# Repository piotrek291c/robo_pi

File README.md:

# robo_pi

http://forbot.pl/blog/artykuly/teoria/jak-zaimplementowac-regulator-pid-dla-silnika-z-enkoderem-id6310
http://www.forbot.pl/forum/topics20/teoria-sterowanie-silnikiem-robotem-pid-vt2055.htm
http://forbot.pl/blog/artykuly/programowanie/sterowanie-robotem-mobilnym-klasy-20-id2708

http://www.forbot.pl/forum/topics43/pomoc-w-doborze-silnika-do-robota-vt6278.htm

https://oscarliang.com/raspberry-pi-color-tracking-opencv-pid/

https://oscarliang.com/raspberry-pi-color-tracking-opencv-pid/

http://robot-kingdom.com/pid-controller-tutorial-for-robots/

http://home.agh.edu.pl/~kwant/wordpress/wp-content/uploads/Praca-in%C5%BCynierska-Mateusz-Skalski.pdf

http://www.forbot.pl/forum/topics20/teoria-sterowanie-silnikiem-robotem-pid-vt2055.htm

http://forum.r-pi.pl/python/regulator-pid-t150544.html

https://github.com/DexterInd?tab=repositories

http://mikrokontrolery.blogspot.com/2011/03/Robotyka-Teoria-Predkosc-obrotowa-oraz-kierunek-obrotu-kol.html

http://www.jarzebski.pl/arduino/czujniki-i-sensory/3-osiowy-magnetometr-hmc5883l.html

https://projects.drogon.net/raspberry-pi/wiringpi/i2c-library/

https://github.com/sanzaru/hmc5883l

https://github.com/mwilliams03/BerryIMU

https://github.com/STMemsLinuxDrivers/lsm6ds3-input/blob/master/drivers/input/misc/lsm6ds3/lsm6ds3_i2c.c

https://github.com/sparkfun/SparkFun_LSM6DS3_Arduino_Library

http://raspberrypiprogramming.blogspot.com/2014/08/how-to-install-and-setup-qt-creator-on.html

http://raspberrypiprogramming.blogspot.com/2014/08/how-to-install-and-setup-qt-creator-on.html

https://blogs.ncl.ac.uk/francisfranklin/2014/04/16/using-i2c-with-the-raspberry-pi-step-2-sparkfun-9dof-sensor-stick/
https://github.com/jrowberg/i2cdevlib/tree/master/RaspberryPi_bcm2835
https://github.com/sparkfun/LSM6DS3_Breakout/blob/master/Libraries/Arduino/examples/MinimalistExample/MinimalistExample.ino

https://github.com/jrowberg/i2cdevlib
https://github.com/FJFranklin/i2cdevlib

https://github.com/mwbritton/Raspberry-Pi-4x4-in-Schools-Project/blob/master/LSM6DS3.py

https://github.com/sparkfun/SparkFun_LSM6DS3_Arduino_Library

https://github.com/me-no-dev/RasPiArduino

http://www.instructables.com/id/Building-a-segway-in-Raspberry-Pi/?ALLSTEPS

https://www.sunfounder.com/learn/sensor-kit-v2-0-for-raspberry-pi-b-plus/lesson-32-mpu6050-gyro-acceleration-sensor-sensor-kit-v2-0-for-b-plus.html

https://github.com/jrowberg/i2cdevlib/tree/master/RaspberryPi_bcm2835

https://github.com/jrowberg/i2cdevlib/tree/master/Arduino/MPU6050

https://github.com/mwilliams03/Raspberry-Gyro-Acc

http://www.jarzebski.pl/arduino/czujniki-i-sensory/czujnik-wilgotnosci-i-temperatury-dht11-dht22.html

http://www.raspberrypi-spy.co.uk/2013/10/analogue-sensors-on-the-raspberry-pi-using-an-mcp3008/

http://shaunsbennett.com/piblog/?p=266

https://github.com/halherta/RaspberryPi-mcp3008Spi

https://pimylifeup.com/raspberry-pi-webcam-server/

https://blog.miguelgrinberg.com/post/stream-video-from-the-raspberry-pi-camera-to-web-browsers-even-on-ios-and-android

https://blog.miguelgrinberg.com/post/how-to-build-and-run-mjpg-streamer-on-the-raspberry-pi

http://www.pyimagesearch.com/2015/03/30/accessing-the-raspberry-pi-camera-with-opencv-and-python/

https://github.com/ccrisan/motionpie/wiki/Fast-Network-Camera
https://blog.ligos.net/2016-04-17/RaspberryPi-As-A-Simple-MJPEG-Camera.html

http://www.howtoembed.com/projects/raspberry-pi/95-motioneye-with-raspberry-pi
https://github.com/ccrisan/motioneye/wiki/Install-On-Raspbian
https://programmaticponderings.com/2013/01/01/remote-motion-activated-web-based-video-surveillance-with-raspberry-pi/
http://pingbin.com/2012/12/raspberry-pi-web-cam-server-motion/

http://www.ostafichuk.com/raspberry-pi-projects/raspimower/fast-web-video-streaming-for-the-raspberry-pi/

https://github.com/dbblackdiamond/SparkFun-LSM6DS3-Photon

http://avrkwiat.nstrefa.pl/omnie/index.php?option=com_content&view=article&id=171&Itemid=195

https://github.com/sparkfun/SparkFun_LSM6DS3_Arduino_Library
http://robotics.stackexchange.com/questions/8680/calculating-position-based-on-accelerometer-data

http://www.starlino.com/imu_guide.html
http://perso-etis.ensea.fr/~pierandr/cours/M1_SIC/AN3397.pdf
http://aeroquad.com/showthread.php?7786-Simple-paper-about-an-algorithm-for-positioning-using-accelerometers

https://github.com/sparkfun/SparkFun_LSM6DS3_Arduino_Library/blob/master/src/SparkFunLSM6DS3.h

https://github.com/sparkfun/SparkFun_LSM6DS3_Arduino_Library/blob/master/src/SparkFunLSM6DS3.cpp

https://github.com/sparkfun/SparkFun_LSM6DS3_Arduino_Library/blob/master/examples/MinimalistExample/MinimalistExample.ino

https://github.com/dbblackdiamond/SparkFun-LSM6DS3-Photon/blob/master/firmware/SparkFun-LSM6DS3-Photon.h

http://pdf1.alldatasheet.net/datasheet-pdf/view/796179/STMICROELECTRONICS/LSM6DS3.html

http://avrkwiat.nstrefa.pl/omnie/index.php?option=com_content&view=article&id=245&Itemid=273

http://starter-kit.nettigo.pl/2013/03/robo-starter-kit-czyli-pierwsze-kroki-z-robotyka-line-follower/

http://akademia.nettigo.pl/playlist/robokit_od_nettigo.html

http://uczymy.edu.pl/wp/blog/2015/07/13/transoptor-szczelinowy/

https://botland.com.pl/transoptory-odbiciowe/52-czujnik-transoptor-odbiciowy-cny70.html

http://fritzing.org/media/fritzing-repo/projects/a/arduino-cny70-light-proximity-sensor/images/CNY70%20light%20proximity%20sensor_bb.png

https://github.com/cvra/odometry
https://github.com/srv/stereo_slam
http://automation.tkk.fi/attach/AS-0-2230/odometry.c.txt

http://rossum.sourceforge.net/papers/CalculationsForRobotics/CompendiumForKinematics.htm
https://github.com/eschulma/robot-libraries-arduino
https://arxiv.org/pdf/1509.02154.pdf
http://www.geology.smu.edu/dpa-www/robots/doc/odometry.txt
http://robotics.stackexchange.com/questions/1653/calculate-position-of-differential-drive-robot
http://robotics.stackexchange.com/questions/8693/how-to-perform-odometry-on-an-arduino-for-a-differential-wheeled-robot?rq=1
http://robotics.stackexchange.com/questions/8931/how-to-combine-odometry-information-with-time-shifted-information-from-imu?rq=1
https://firstinmaryland.org/images/stories/documents2013/2013_Educ_Day/Sensors_Presentation.pdf
http://kt.era.ee/supervision/Kallas2013.pdf
http://automation.tkk.fi/attach/AS-0-2230/odometry.c.txt
https://github.com/cvra/odometry

https://app.assembla.com/spaces/robot-autonomiczny/documents/b6JUyuJDir4ii4eJe5cbCb/download/b6JUyuJDir4ii4eJe5cbCb
http://lirec.iiar.pwr.edu.pl/~konarch/download/inne_roboty/zdarzenia_koncowe.pdf
https://app.assembla.com/spaces/robot-autonomiczny/documents/b6JUyuJDir4ii4eJe5cbCb/download/b6JUyuJDir4ii4eJe5cbCb

http://raspberrypi.stackexchange.com/questions/8851/setting-up-wifi-and-ethernet
https://sites.google.com/site/raspberryflightgear/4-qt-and-raspberry
https://www.raspberrypi.org/forums/viewtopic.php?t=33881
http://www.aoakley.com/articles/2013-07-31-raspberry-pi-networking.php

http://mdiy.pl/pcb-lutowanie-przelotek/
http://www.elektroda.pl/rtvforum/topic100099.html

http://rab.ict.pwr.wroc.pl/~arent/rr/mpr/czujniki0.html

http://howtomechatronics.com/projects/arduino-radar-project/

https://www.youtube.com/watch?v=I5nAynPdNJY

http://samselectronicsprojects.blogspot.com/2014/07/getting-roll-pitch-and-yaw-from-mpu-6050.html
http://www.jarzebski.pl/arduino/rozwiazania-i-algorytmy/odczyty-pitch-roll-oraz-filtr-kalmana.html
https://forum.arduino.cc/index.php?topic=407756.0
http://perso-etis.ensea.fr/%7Epierandr/cours/M1_SIC/AN3397.pdf

https://rasspberrypi.wordpress.com/2012/09/09/wifi-tools-for-raspberry-pi/

http://starter-kit.nettigo.pl/2012/02/akcelerometry-zyroskopy-i-kompasy-czyli-badanie-polozenia-z-arduino-cz-1/

https://pimylifeup.com/raspberry-pi-webcam-server/

https://www.element14.com/community/community/raspberry-pi/raspberrypi_projects/blog/2016/04/25/noir-v2-video-streaming-baby-monitor

https://blog.miguelgrinberg.com/post/stream-video-from-the-raspberry-pi-camera-to-web-browsers-even-on-ios-and-android

https://programmaticponderings.com/2013/01/01/remote-motion-activated-web-based-video-surveillance-with-raspberry-pi/

https://pimylifeup.com/raspberry-pi-security-camera/

https://www.element14.com/community/community/raspberry-pi/raspberrypi_projects/blog/2016/04/25/noir-v2-video-streaming-baby-monitor

http://www.raspberry-pi-geek.com/Archive/2016/15/Using-the-RPi-Cam-Web-Interface

https://neverbenever.wordpress.com/2015/02/11/how-to-autostart-a-program-in-raspberry-pi-or-linux/

http://elinux.org/RPi-Cam-Web-Interface

http://raspberrypi.stackexchange.com/questions/28199/raspberry-pi-starting-programs-automatically-on-startup

https://www.domoticz.com/forum/viewtopic.php?t=16852

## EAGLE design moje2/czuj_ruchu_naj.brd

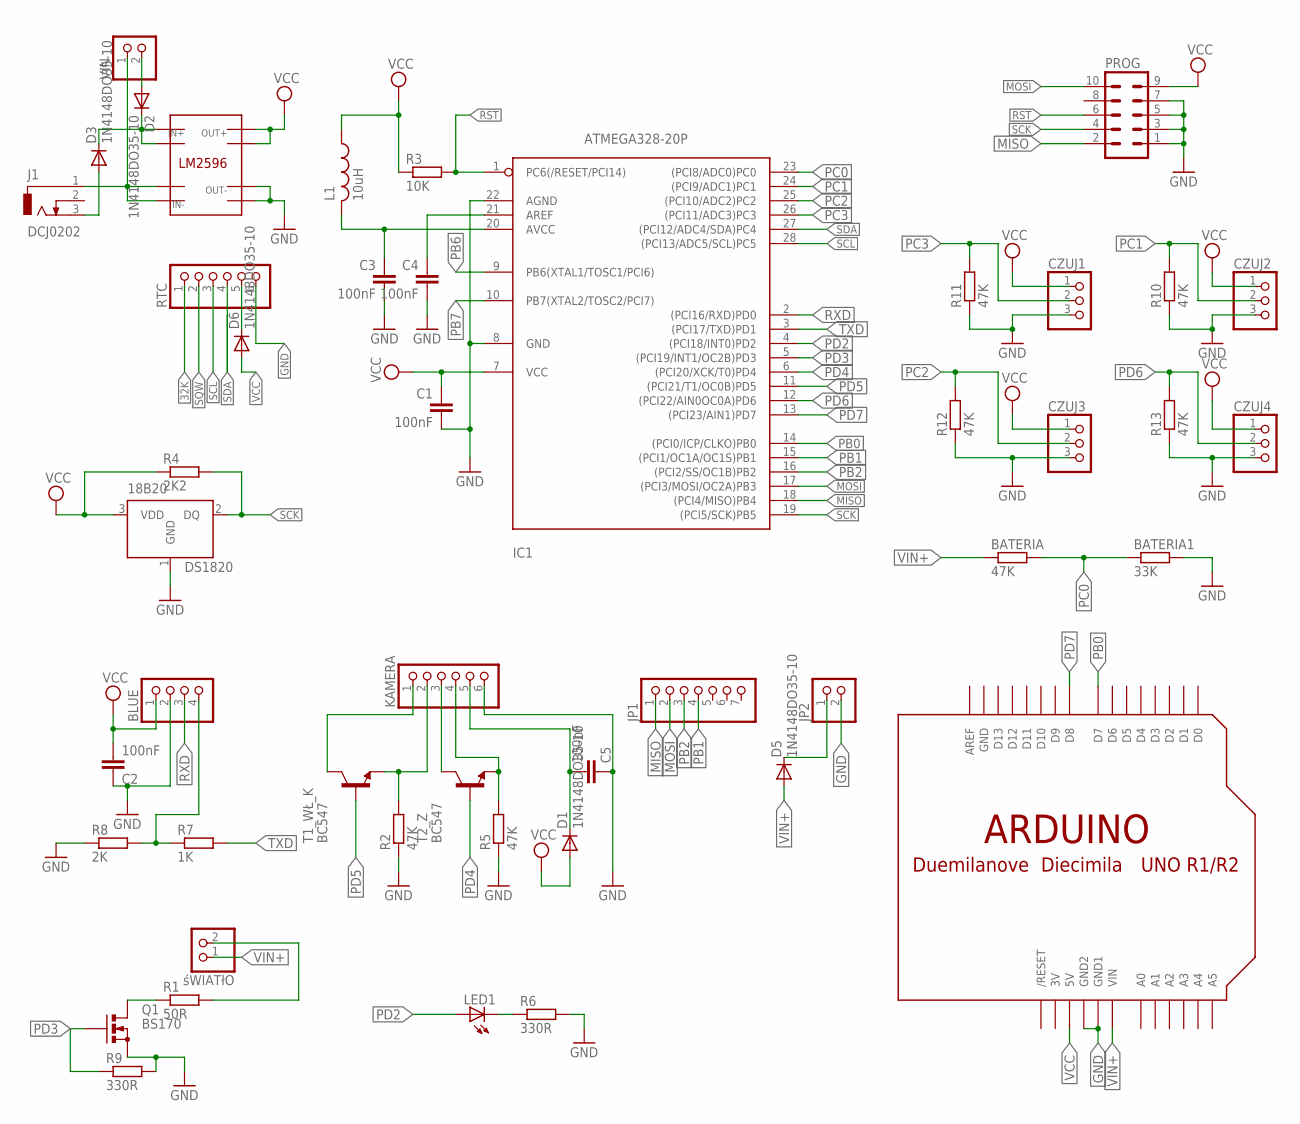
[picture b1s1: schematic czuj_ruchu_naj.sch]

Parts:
18B20: DS1820; TO-92
BATERIA: 47K; 0204/7
BATERIA1: 33K; 0204/7
BLUE: PINHD-1X4; 1X04
C1, C2, C3, C4, C5: 100nF; C2.5-3
CZUJ1, CZUJ2, CZUJ3, CZUJ4: PINHD-1X3; 1X03
D1, D2, D3, D5, D6: 1N4148DO35-10; DO35-10
IC1: ATMEGA328-20P; DIL28-3
J1: DCJ0202
JP1: PINHD-1X7/90; 1X07/90
JP2: PINHD-1X2/90; 1X02/90
KAMERA: PINHD-1X6/90; 1X06/90
L1: 10uH; 6000-XXXX-RC
LED1: LED5MM
PROG: MA05-2
Q1: BS170; SOT54E
R1: 50R; 0204/7
R2, R5, R10, R11, R12, R13: 47K; 0204/7
R3: 10K; 0204/7
R4: 2K2; 0204/7
R6, R9: 330R; 0204/7
R7: 1K; 0204/7
R8: 2K; 0204/7
RTC: PINHD-1X6/90; 1X06/90
T1_WŁ_K, T2_Z: BC547; TO92
U$1: ARDUINO-NOHOLE
VIN: PINHD-1X2; 1X02
ZASILANIE: LM2596; LM25
śWIATłO: PINHD-1X2; 1X02

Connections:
3V: U$1.3V
32K: RTC.1
GND: 18B20.1 (GND), BATERIA1.2, BLUE.2, C1.2, C2.1, C3.2, C4.2, C5.1, CZUJ1.3, CZUJ2.3, CZUJ3.3, CZUJ4.3, IC1.8 (GND), IC1.22 (AGND), JP2.2, KAMERA.6, PROG.1, PROG.3, PROG.5, PROG.7, Q1.S, R2.1, R5.1, R6.2, R8.1, R9.2, R10.1, R11.1, R12.1, R13.1, RTC.6, U$1.GND, U$1.GND1, U$1.GND2, ZASILANIE.OUT-, ZASILANIE.OUT-. (OUT_)
MISO: IC1.18 ((PCI4/MISO)PB4), JP1.1, PROG.2
MOSI: IC1.17 ((PCI3/MOSI/OC2A)PB3), JP1.2, PROG.10
unnamed: Q1.D, R1.1
unnamed: D2.A, VIN.2
unnamed: KAMERA.1, T1_WŁ_K.3 (C)
unnamed: R1.2, śWIATłO.2
unnamed: C3.1, IC1.20 (AVCC), L1.2
unnamed: C4.1, IC1.21 (AREF)
unnamed: KAMERA.3, T2_Z.3 (C)
unnamed: C5.2, D1.C, KAMERA.5
unnamed: D3.A, J1.3
unnamed: LED1.K (C), R6.1
unnamed: KAMERA.2, R2.2, T1_WŁ_K.1 (E)
unnamed: KAMERA.4, R5.2, T2_Z.1 (E)
unnamed: D6.C, RTC.5
PB0: IC1.14 ((PCI0/ICP/CLKO)PB0), U$1.D7
PB1: IC1.15 ((PCI1/OC1A/OC1S)PB1), JP1.4
PB2: IC1.16 ((PCI2/SS/OC1B)PB2), JP1.3
PB6: IC1.9 (PB6(XTAL1/TOSC1/PCI6))
PB7: IC1.10 (PB7(XTAL2/TOSC2/PCI7))
PC0: BATERIA.2, BATERIA1.1, IC1.23 ((PCI8/ADC0)PC0)
PC1: CZUJ2.2, IC1.24 ((PCI9/ADC1)PC1), R10.2
PC2: CZUJ3.2, IC1.25 ((PCI10/ADC2)PC2), R12.2
PC3: CZUJ1.2, IC1.26 ((PCI11/ADC3)PC3), R11.2
PD2: IC1.4 ((PCI18/INT0)PD2), LED1.A
PD3: IC1.5 ((PCI19/INT1/OC2B)PD3), Q1.G, R9.1
PD4: IC1.6 ((PCI20/XCK/T0)PD4), T2_Z.2 (B)
PD5: IC1.11 ((PCI21/T1/OC0B)PD5), T1_WŁ_K.2 (B)
PD6: CZUJ4.2, IC1.12 ((PCI22/AIN0OC0A)PD6), R13.2
PD7: IC1.13 ((PCI23/AIN1)PD7), U$1.D8
RST: IC1.1 (PC6(/RESET/PCI14)), PROG.6, R3.2
RXD: BLUE.3, IC1.2 ((PCI16/RXD)PD0)
SCK: 18B20.2 (DQ), IC1.19 ((PCI5/SCK)PB5), PROG.4, R4.2
SCL: IC1.28 ((PCI13/ADC5/SCL)PC5), RTC.3
SDA: IC1.27 ((PCI12/ADC4/SDA)PC4), RTC.4
SQW: RTC.2
TXD: IC1.3 ((PCI17/TXD)PD1), R7.2
TXDB: BLUE.4, R7.1, R8.2
VCC: 18B20.3 (VDD), BLUE.1, C1.1, C2.2, CZUJ1.1, CZUJ2.1, CZUJ3.1, CZUJ4.1, D1.A, D6.A, IC1.7 (VCC), L1.1, PROG.9, R3.1, R4.1, U$1.5V, ZASILANIE.OUT+, ZASILANIE.OUT+.
VCCS1: D5.C, JP2.1
VIN+: BATERIA.1, D2.C, D3.C, D5.A, U$1.VIN, ZASILANIE.IN+, ZASILANIE.IN+., śWIATłO.1
VIN-: J1.1, VIN.1, ZASILANIE.IN-, ZASILANIE.IN-.

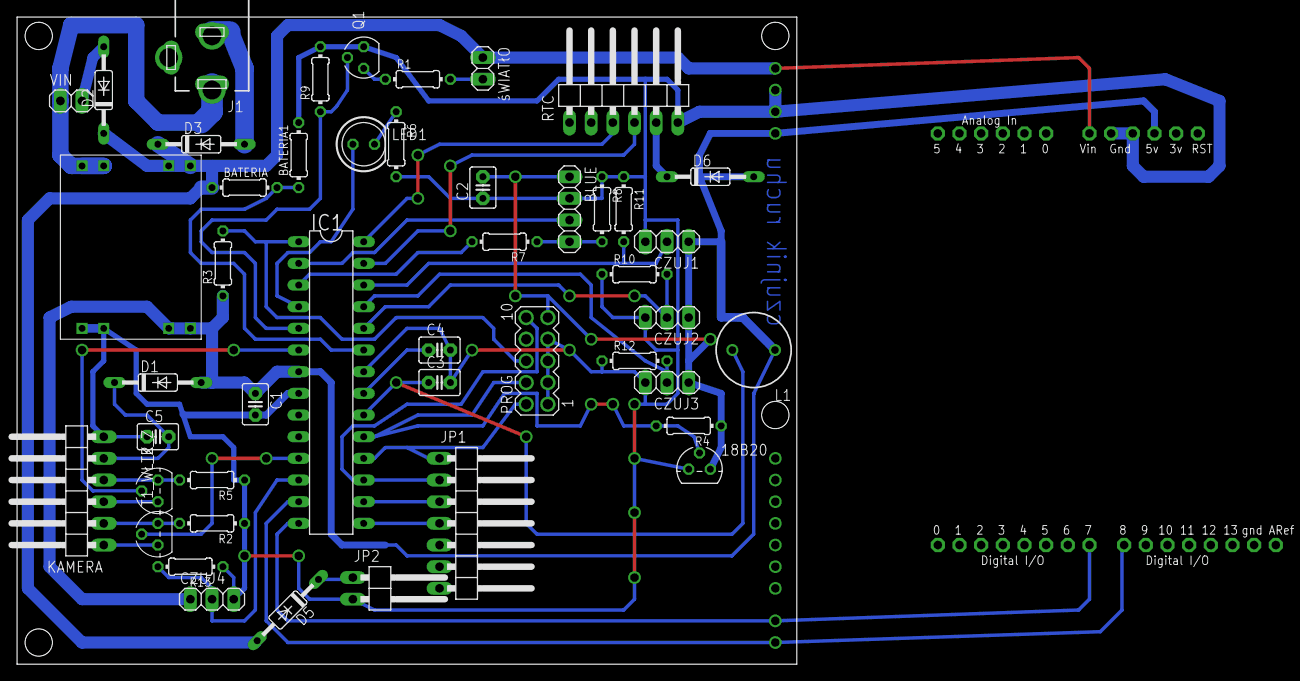
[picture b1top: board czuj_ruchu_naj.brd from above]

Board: 2 copper layers, 91.4 x 75.9 mm, 47 parts (0 on the bottom side), 40 nets.

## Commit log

2016-12-03 Create file
2016-12-06 Create lsm6
2016-12-16 qt_robo
    qt_robo
2016-12-16 qt
    projekt qt z bledami polaczenia ale rysuje trase
2016-12-16 qt2
    qt2
2016-12-17 qt_robo3
    qt_robo3
2016-12-17 qt_robo3a
    qt_robo3a
2017-02-08 robo_3 takie
    a
2017-02-22 pcmainwindow
2017-02-22 pimainwindow
2017-02-22 pc_mainwindow2
2017-02-22 pimainwindow2
2017-03-06 fl_fuzzy
2017-03-06 fuzzy_lite
2017-03-14 robot_14_03_2017r
    robot
